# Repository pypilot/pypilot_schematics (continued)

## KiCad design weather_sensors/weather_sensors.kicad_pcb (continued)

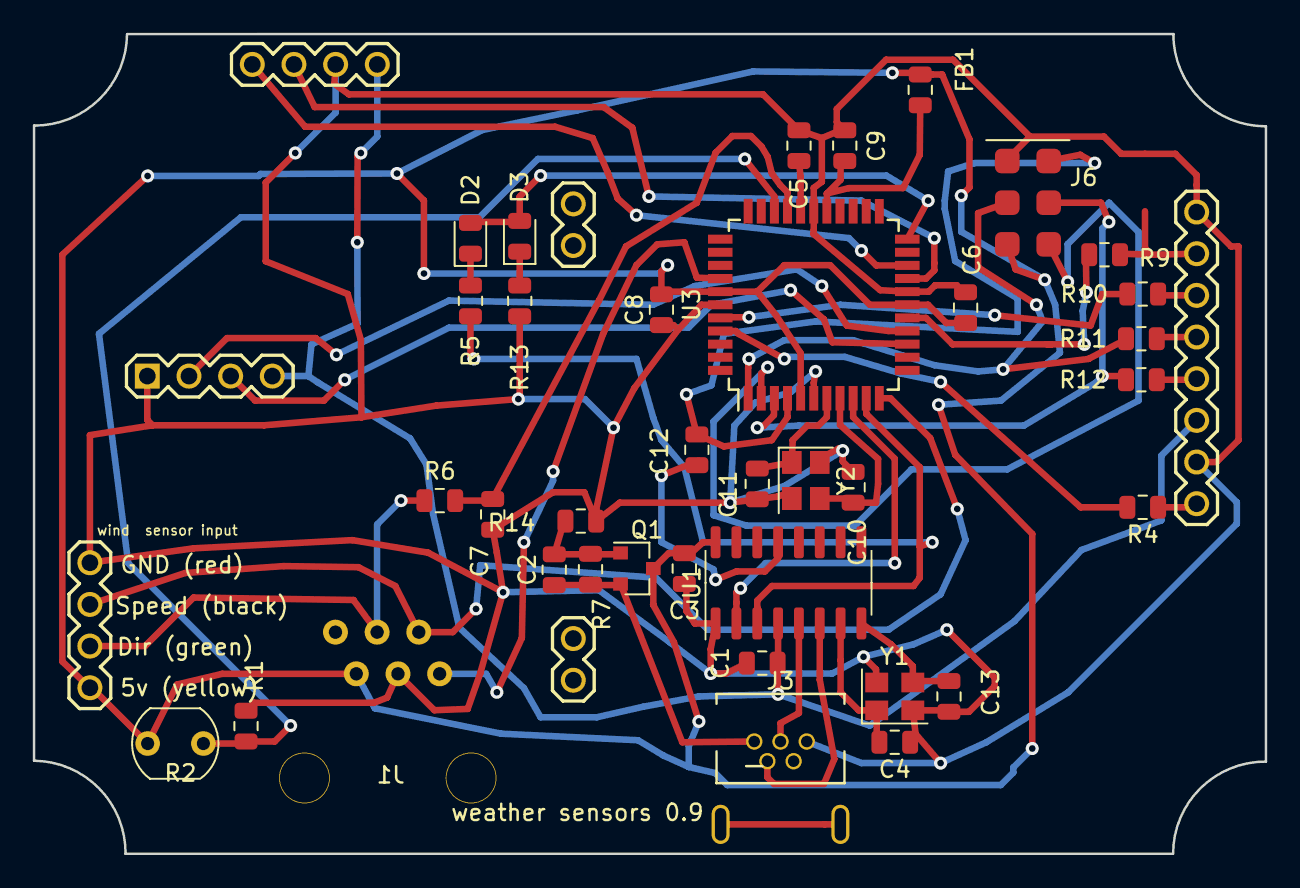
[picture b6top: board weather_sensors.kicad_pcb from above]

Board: 2 copper layers, 75.1 x 50.0 mm, 42 parts (1 on the bottom side), 40 nets.

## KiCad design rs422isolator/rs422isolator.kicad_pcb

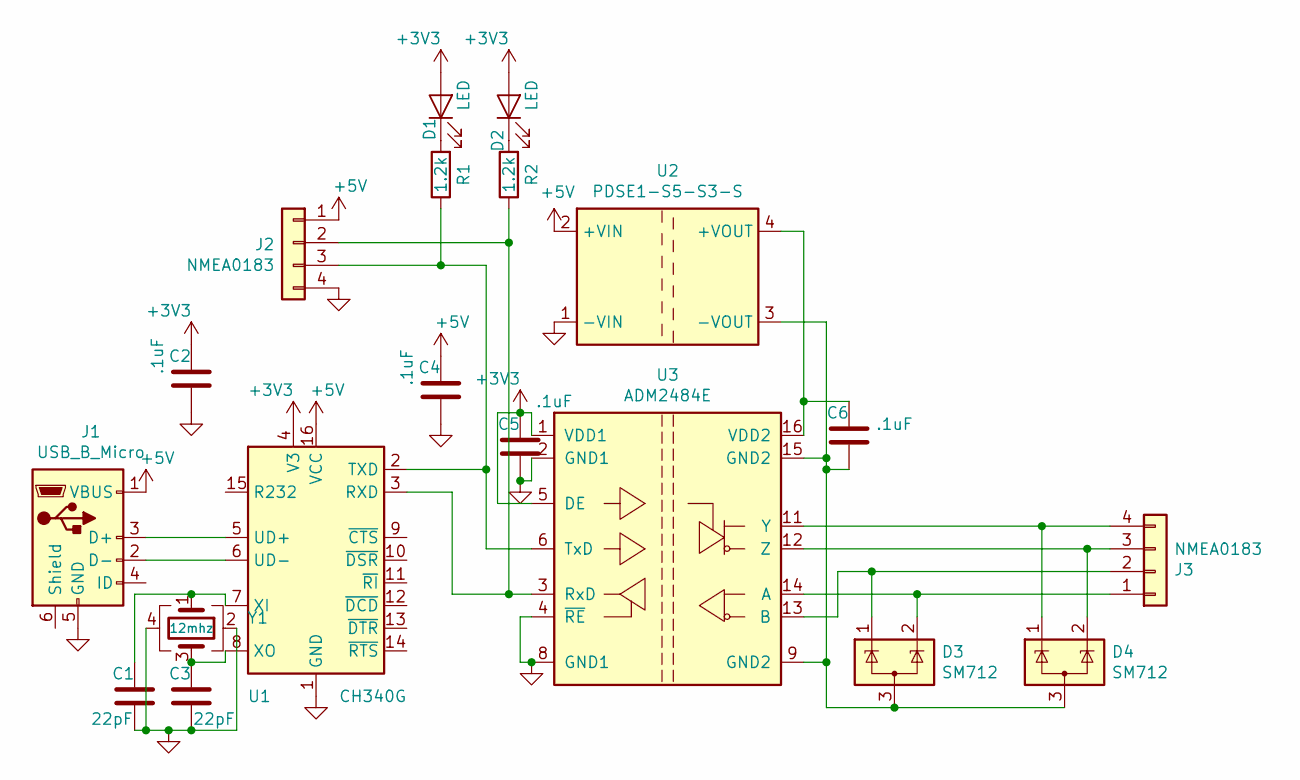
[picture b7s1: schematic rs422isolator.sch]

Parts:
C1, C3: 22pF; C_0805_2012Metric; LCSC C1804
C2, C4, C5, C6: .1uF; C_0805_2012Metric; LCSC C49678
D1: LED; LED_0805_2012Metric; LCSC C2297
D2: LED; LED_0805_2012Metric; LCSC C2296
D3, D4: SM712; SOT-23; LCSC C32677
J1: USB_B_Micro; USB_Mini-B_Tensility_54-00023_Vertical
J2: NMEA0183; PinHeader_1x04_P2.54mm_Vertical
J3: NMEA0183; rs422connector
R1, R2: 1.2k; R_0805_2012Metric; LCSC C17379
U1: CH340G; SOIC-16_3.9x9.9mm_P1.27mm; LCSC C14267
U2: PDSE1-S5-S3-S; Converter_DCDC_muRata_CRE1xxxxxx3C_THT
U3: ADM2484E; SOIC-16W_7.5x10.3mm_P1.27mm; LCSC C60412
Y1: 12mhz; Crystal_SMD_3225-4Pin_3.2x2.5mm; LCSC C9002

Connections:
+3V3: C2.1, C5.1, D1.2 (A), D2.2 (A), U1.4 (V3), U3.1 (VDD1), U3.5 (DE)
+5V: C4.1, J1.1 (VBUS), J2.1, U1.16 (VCC), U2.2 (+VIN)
GND: C1.2, C2.2, C3.2, C4.2, C5.2, J1.5 (GND), J2.4, U1.1 (GND), U2.1 (-VIN), U3.2 (GND1), U3.4 (~RE), U3.8 (GND1), Y1.2, Y1.4
unnamed: C1.1, U1.7 (XI), Y1.1
unnamed: C3.1, U1.8 (XO), Y1.3
unnamed: C6.1, U2.4 (+VOUT), U3.16 (VDD2)
unnamed: C6.2, D3.3 (A), D4.3 (A), U2.3 (-VOUT), U3.9 (GND2), U3.15 (GND2)
unnamed: D1.1 (K), R1.2
unnamed: D2.1 (K), R2.2
unnamed: D3.1 (K), J3.2, U3.13 (B)
unnamed: D3.2 (K), J3.1, U3.14 (A)
unnamed: D4.1 (K), J3.4, U3.11 (Y)
unnamed: D4.2 (K), J3.3, U3.12 (Z)
unnamed: J1.2 (D-), U1.6 (UD-)
unnamed: J1.3 (D+), U1.5 (UD+)
unnamed: J2.2, R2.1, U1.3 (RXD), U3.3 (RxD)
unnamed: J2.3, R1.1, U1.2 (TXD), U3.6 (TxD)

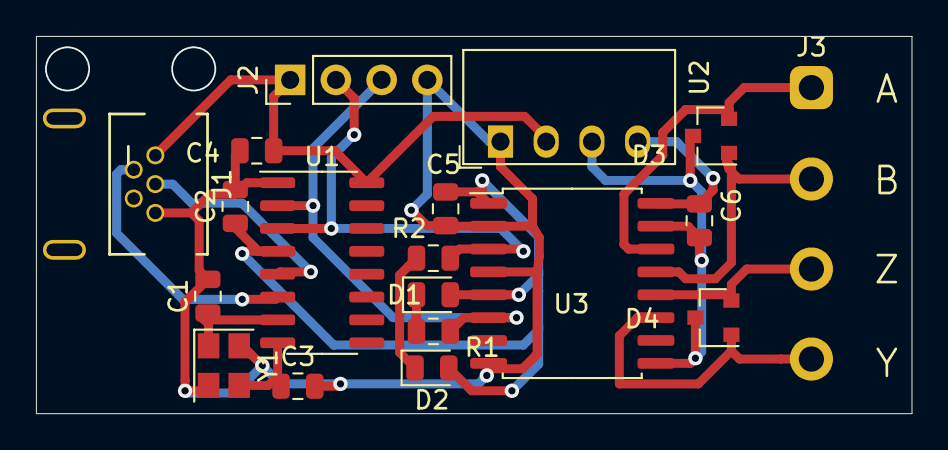
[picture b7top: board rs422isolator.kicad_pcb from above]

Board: 2 copper layers, 48.6 x 21.0 mm, 19 parts (0 on the bottom side), 17 nets.

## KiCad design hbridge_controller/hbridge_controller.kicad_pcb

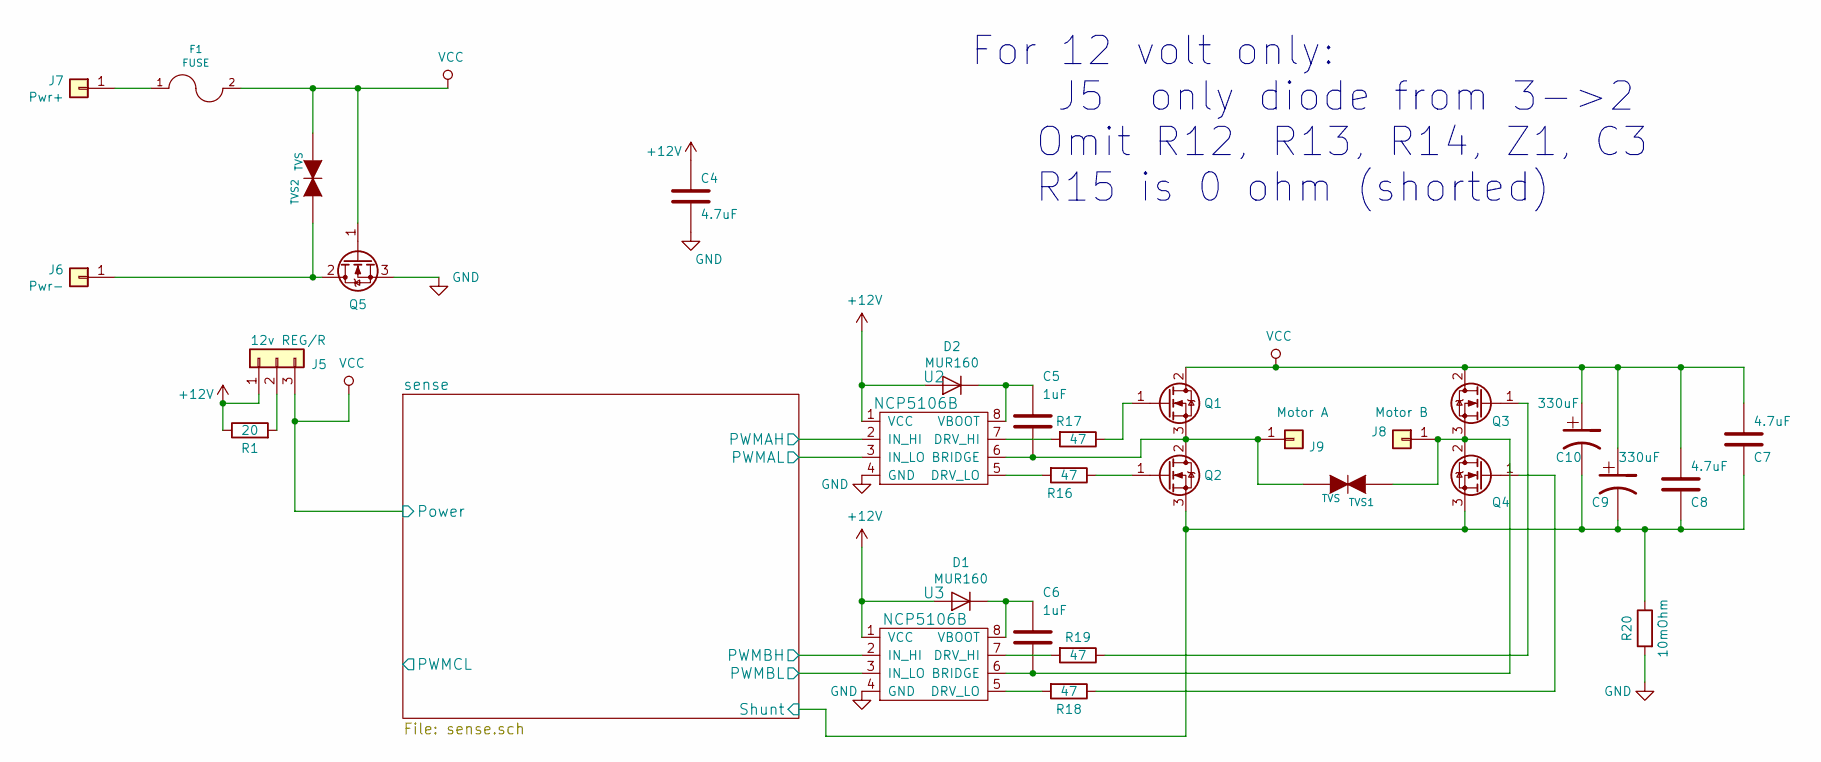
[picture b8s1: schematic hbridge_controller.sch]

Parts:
C4: 4.7uF; C_Disc_D5.0mm_W2.5mm_P2.50mm
C5, C6: 1uF; C_Disc_D7.0mm_W2.5mm_P5.00mm
C7, C8: 4.7uF; C_Disc_D8.0mm_W2.5mm_P5.00mm
C9, C10: 330uF; CP_Radial_D10.0mm_P5.00mm
D1, D2: MUR160; D_T-1_P2.54mm_Vertical_AnodeUp
F1: FUSE; BladeFuse-CarType
J5: 12v REG/R; TO-220-3_Vertical
J6: Pwr-; screw_terminal
J7: Pwr+; screw_terminal
J8: Motor B; Power
J9: Motor A; Power
Q1, Q2, Q3, Q4, Q5: Q_NMOS_GDS; TO-220-3_Vertical
R1: 20; R_Axial_DIN0204_L3.6mm_D1.6mm_P5.08mm_Horizontal
R16, R17, R18, R19: 47; R_Axial_DIN0204_L3.6mm_D1.6mm_P2.54mm_Vertical
R20: 10mOhm; Resistors_Horizontal_RM10mm
TVS1: TVS; tvs
TVS2: TVS; DIODE-1N4001
U2, U3: NCP5106B; DIP-8_W7.62mm

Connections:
+12V: C4.1, D1.2 (A), D2.2 (A), J5.1, R1.1, U2.1 (VCC), U3.1 (VCC); also elsewhere on the board
/sense/PWMAH: U2.2 (IN_HI); also elsewhere on the board
/sense/PWMAL: U2.3 (IN_LO); also elsewhere on the board
/sense/PWMBH: U3.2 (IN_HI); also elsewhere on the board
/sense/PWMBL: U3.3 (IN_LO); also elsewhere on the board
/sense/Shunt: C7.2, C8.2, C9.2 (-), C10.2 (-), Q2.3 (S), Q4.3 (S), R20.1; also elsewhere on the board
GND: C4.2, Q5.3 (S), R20.2, U2.4 (GND), U3.4 (GND); also elsewhere on the board
unnamed: C5.1, D2.1 (K), U2.8 (VBOOT)
unnamed: C5.2, J9.1, Q1.3 (S), Q2.2 (D), TVS1.K, U2.6 (BRIDGE)
unnamed: C6.1, D1.1 (K), U3.8 (VBOOT)
unnamed: C6.2, J8.1, Q3.3 (S), Q4.2 (D), TVS1.A, U3.6 (BRIDGE)
unnamed: F1.1, J7.1
unnamed: J5.2, R1.2
unnamed: J6.1, Q5.2 (D), TVS2.A
unnamed: Q1.1 (G), R17.1
unnamed: Q2.1 (G), R16.1
unnamed: Q3.1 (G), R19.1
unnamed: Q4.1 (G), R18.1
unnamed: R16.2, U2.5 (DRV_LO)
unnamed: R17.2, U2.7 (DRV_HI)
unnamed: R18.2, U3.5 (DRV_LO)
unnamed: R19.2, U3.7 (DRV_HI)
VCC: C7.1, C8.1, C9.1 (+), C10.1 (+), F1.2, J5.3, Q1.2 (D), Q3.2 (D), Q5.1 (G), TVS2.K; also elsewhere on the board

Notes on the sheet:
For 12 volt only: J5 only diode from 3->2 Omit R12, R13, R14, Z1, C3 R15 is 0 ohm (shorted)

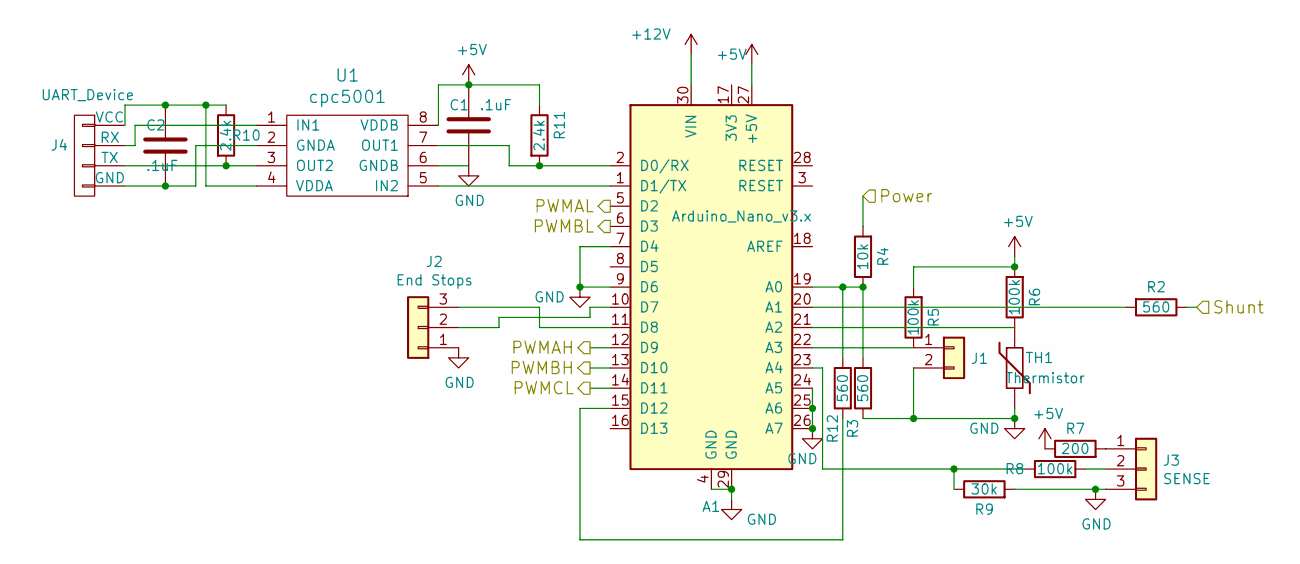
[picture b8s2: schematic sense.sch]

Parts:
A1: Arduino_Nano_v3.x; arduino_mini
C1, C2: .1uF; C_Disc_D7.0mm_W2.5mm_P5.00mm
J1: Conn_01x02; PinSocket_1x02_P2.54mm_Vertical
J2: End Stops; PinHeader_1x03_P2.54mm_Vertical
J3: SENSE; PinSocket_1x03_P2.54mm_Vertical
J4: UART_Device; uart
R2, R3, R12: 560; R_Axial_DIN0204_L3.6mm_D1.6mm_P5.08mm_Horizontal
R4: 10k; R_Axial_DIN0204_L3.6mm_D1.6mm_P5.08mm_Horizontal
R5, R6, R8: 100k; R_Axial_DIN0204_L3.6mm_D1.6mm_P5.08mm_Horizontal
R7: 200; R_Axial_DIN0204_L3.6mm_D1.6mm_P5.08mm_Horizontal
R9: 30k; R_Axial_DIN0204_L3.6mm_D1.6mm_P5.08mm_Horizontal
R10, R11: 2.4k; R_Axial_DIN0204_L3.6mm_D1.6mm_P5.08mm_Horizontal
TH1: Thermistor; R_Axial_DIN0204_L3.6mm_D1.6mm_P5.08mm_Horizontal
U1: cpc5001; DIP-8_W7.62mm

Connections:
+5V: A1.27 (+5V), C1.1, R5.2, R6.2, R7.1, R11.1, U1.8 (VDDB)
+12V: A1.30 (VIN); also elsewhere on the board
/sense/PWMAH: A1.12 (D9); also elsewhere on the board
/sense/PWMAL: A1.5 (D2); also elsewhere on the board
/sense/PWMBH: A1.13 (D10); also elsewhere on the board
/sense/PWMBL: A1.6 (D3); also elsewhere on the board
/sense/PWMCL: A1.14 (D11)
/sense/Shunt: R2.1; also elsewhere on the board
GND: A1.4 (GND), A1.7 (D4), A1.9 (D6), A1.24 (A5), A1.25 (A6), A1.26 (A7), A1.29 (GND), C1.2, J1.2, J2.1, J3.3, R3.2, R9.2, TH1.2, U1.6 (GNDB); also elsewhere on the board
unnamed: A1.1 (D1/TX), U1.5 (IN2)
unnamed: A1.2 (D0/RX), R11.2, U1.7 (OUT1)
unnamed: A1.10 (D7), J2.2
unnamed: A1.11 (D8), J2.3
unnamed: A1.15 (D12), R12.2
unnamed: A1.19 (A0), R3.1, R4.1, R12.1
unnamed: A1.20 (A1), R2.2
unnamed: A1.21 (A2), R6.1, TH1.1
unnamed: A1.22 (A3), J1.1, R5.1
unnamed: A1.23 (A4), R8.1, R9.1
unnamed: C2.1, J4.1 (VCC), R10.1, U1.4 (VDDA)
unnamed: C2.2, J4.4 (GND), U1.2 (GNDA)
unnamed: J3.1, R7.2
unnamed: J3.2, R8.2
unnamed: J4.2 (RX), U1.1 (IN1)
unnamed: J4.3 (TX), R10.2, U1.3 (OUT2)
VCC: R4.2; also elsewhere on the board

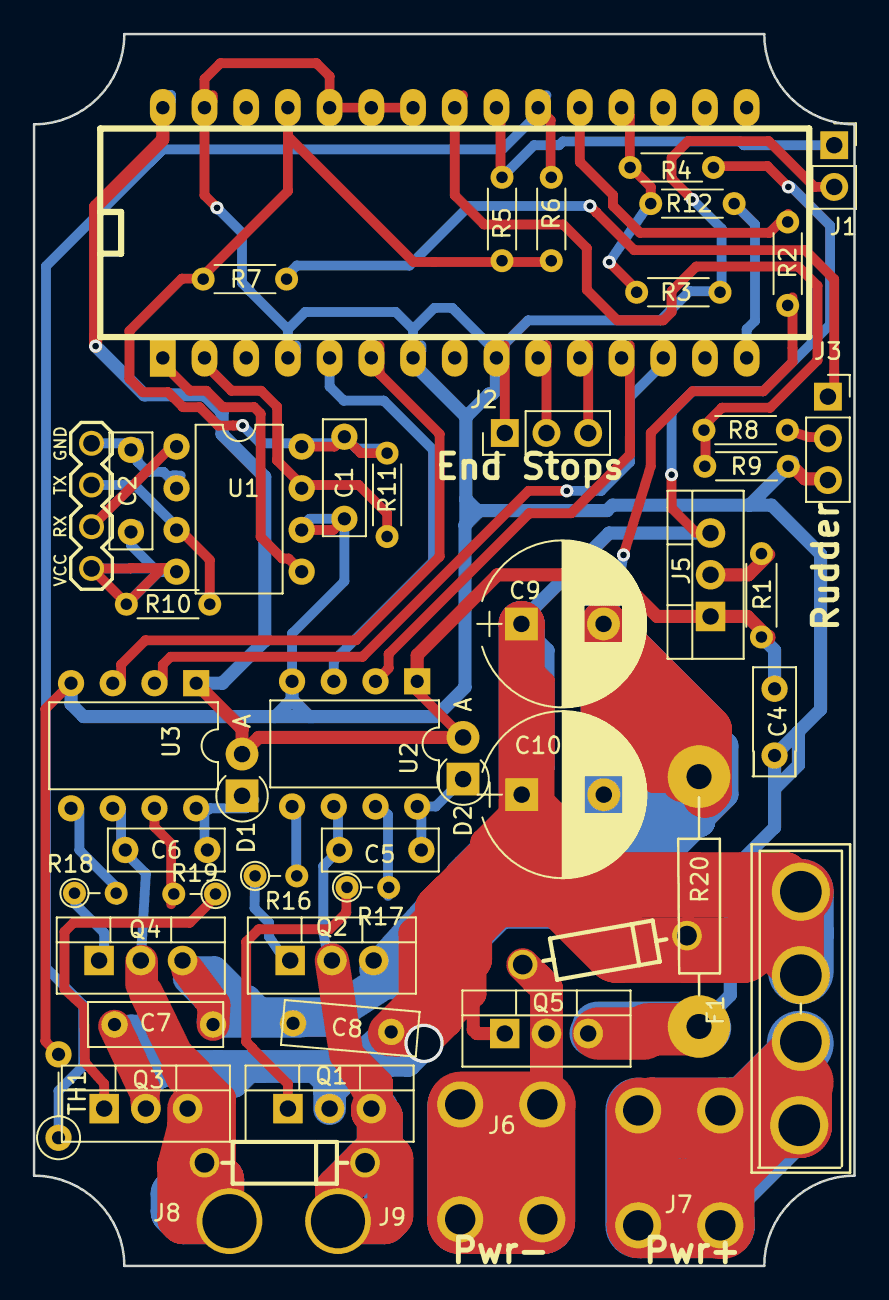
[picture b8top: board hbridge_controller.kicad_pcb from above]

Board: 2 copper layers, 50.0 x 75.0 mm, 50 parts (0 on the bottom side), 40 nets.

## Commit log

2020-08-18 initial commit of kicad repository
2022-05-01 update schematics
2022-06-14 add rf remote control
2023-05-23 add midpower controller
2023-12-03 add weather minimal schematic
